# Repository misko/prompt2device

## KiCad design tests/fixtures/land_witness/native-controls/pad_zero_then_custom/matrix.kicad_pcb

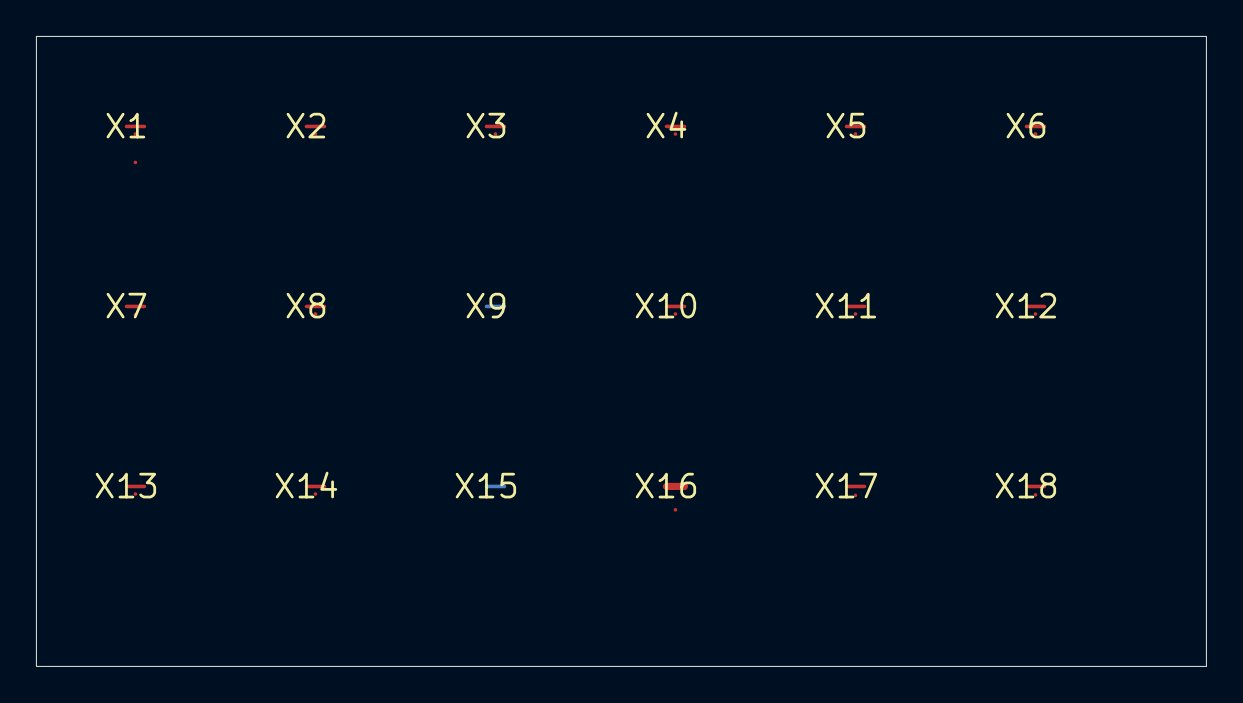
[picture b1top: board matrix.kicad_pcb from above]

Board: 2 copper layers, 65.0 x 35.0 mm, 18 parts (0 on the bottom side), 18 nets.

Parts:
X1: remote_high
X2: b_side
X3: reversal
X4: both_area
X5: offcenter
X6: contained
X7: padpad_guard
X8: track_width
X9: area_layer
X10: last_match
X11: boolean_left
X12: negation
X13: wildcard
X14: multi_constraint
X15: rule_layer
X16: width_transition
X17: oscillation
X18: one_sided

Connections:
area_layer_T: X9.1, X9.2
b_side_T: X2.1, X2.2
boolean_left_T: X11.1, X11.2
both_area_T: X4.1, X4.2
contained_T: X6.1, X6.2
last_match_T: X10.1, X10.2
multi_constraint_T: X14.1, X14.2
negation_T: X12.1, X12.2
offcenter_T: X5.1, X5.2
one_sided_T: X18.1, X18.2
oscillation_T: X17.1, X17.2
padpad_guard_T: X7.1, X7.2
remote_high_T: X1.1, X1.2
reversal_T: X3.1, X3.2
rule_layer_T: X15.1, X15.2
track_width_T: X8.1, X8.2
width_transition_T: X16.1, X16.2
wildcard_T: X13.1, X13.2

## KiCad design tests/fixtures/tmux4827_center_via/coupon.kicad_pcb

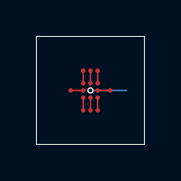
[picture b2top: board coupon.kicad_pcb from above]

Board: 4 copper layers, 6.0 x 6.0 mm, 10 parts (0 on the bottom side), 9 nets.

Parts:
TP_A1: NC_A_P
TP_A2: AUDIO_EN
TP_A3: NC_A_N
TP_B1: ADC_P
TP_B3: ADC_N
TP_C1: FILTER_P
TP_C2: 5V_LDO_HOLD
TP_C3: FILTER_N
TP_GND: GND
U_ISO1: TMUX4827YBHR

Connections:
5V_LDO_HOLD: TP_C2.1, U_ISO1.C2
ADC_N: TP_B3.1, U_ISO1.B3
ADC_P: TP_B1.1, U_ISO1.B1
AUDIO_EN: TP_A2.1, U_ISO1.A2
FILTER_N: TP_C3.1, U_ISO1.C3
FILTER_P: TP_C1.1, U_ISO1.C1
GND: TP_GND.1, U_ISO1.B2
NC_A_N: TP_A3.1, U_ISO1.A3
NC_A_P: TP_A1.1, U_ISO1.A1
